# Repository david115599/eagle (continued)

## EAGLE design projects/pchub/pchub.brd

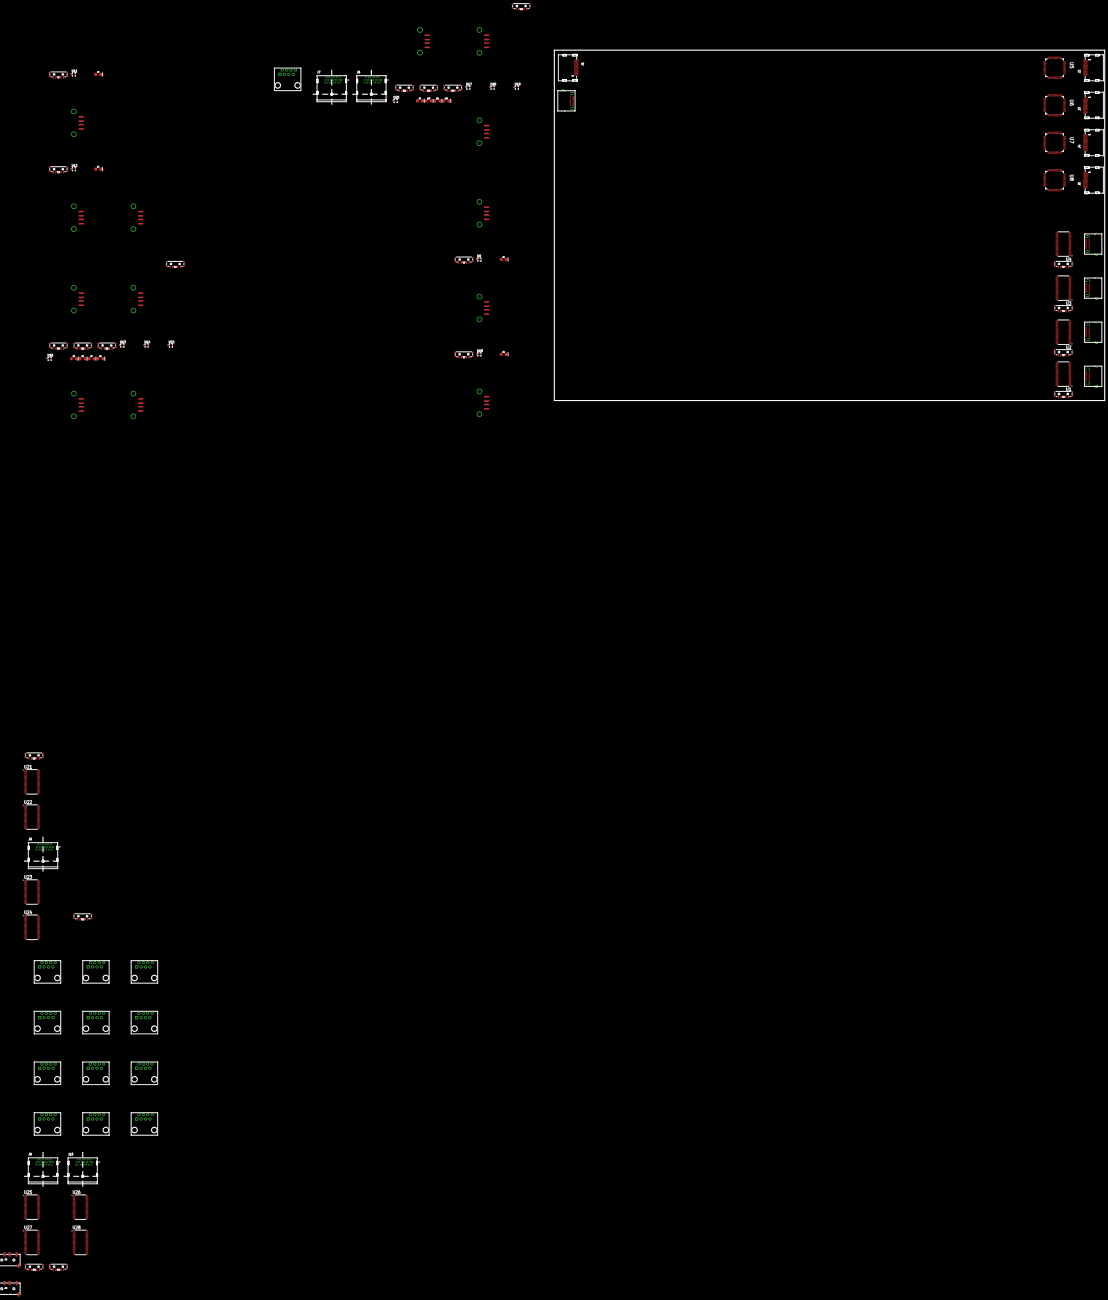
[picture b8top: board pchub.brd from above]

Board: 2 copper layers, 622.8 x 655.0 mm, 103 parts (0 on the bottom side), 383 nets, no tracks yet.

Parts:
D1, D2, D3, D4, D5, D6, D7, D8, D9, D10, D11, D12: FKIT-LED-1206
J1, J2, J3, J4, J5: 685119134923
J6, J7, J8, J9, J10: 2040210-1; TE_2040210-1
J11, J12: AUDIO_JACK_TRRSSMD_RA; AUDIO_JACK_3.5MM_TRRS_SMD_RA
S1, S2, S3, S4, S5, S6, S7, S8, S9, S10, S11, S12, S13, S14, S15, S16, S17, S18, S19, S20: SWITCH_SP3T_SMD
U1, U2, U3, U4, U21, U22, U23, U24, U25, U26, U27, U28: SN74CBT16214DGGR; SOP50P810X120-56N
U5, U6, U7, U8: TMDS361BPAG; QFP50P1200X1200X120-64N
U9, U10, U11, U12, U13, U14, U15, U16, U17, U18, U19, U20: FSUSB63UMX; QFN40P180X180X55-12N
U$1, U$2, U$3, U$4, U$5: USB-TYPE-C; USB-TYPE-C-SMT
U$6, U$19, U$20, U$21, U$22, U$23, U$24, U$25, U$26, U$27, U$28, U$29, U$30: RJ45-8PTH; RJ45-8
X1, X2, X3, X4, X5, X6, X7, X8, X9, X10, X11, X12, X13: USB; USB-A-S-NOSILK-FEMALE

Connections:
5.5V: S1.3, S2.3, S3.3, S4.3, U1.17, U2.17, U3.17, U4.17
B$1: U21.23, U23.23, U25.23, U27.23
B$2: U21.25, U23.25, U25.25, U27.25
CEC: J1.13, J2.13, J3.13, J4.13, J5.13
ETH1: U$6.1, U$19.1, U$20.1, U$21.1, U$22.1, U$23.1, U$24.1, U$25.1, U$26.1, U$27.1, U$28.1, U$29.1, U$30.1
ETH2: U$6.2, U$19.2, U$20.2, U$21.2, U$22.2, U$23.2, U$24.2, U$25.2, U$26.2, U$27.2, U$28.2, U$29.2, U$30.2
ETH3: U$6.3, U$19.3, U$20.3, U$21.3, U$22.3, U$23.3, U$24.3, U$25.3, U$26.3, U$27.3, U$28.3, U$29.3, U$30.3
ETH4: U$6.4, U$19.4, U$20.4, U$21.4, U$22.4, U$23.4, U$24.4, U$25.4, U$26.4, U$27.4, U$28.4, U$29.4, U$30.4
ETH5: U$6.5, U$19.5, U$20.5, U$21.5, U$22.5, U$23.5, U$24.5, U$25.5, U$26.5, U$27.5, U$28.5, U$29.5, U$30.5
ETH6: U$6.6, U$19.6, U$20.6, U$21.6, U$22.6, U$23.6, U$24.6, U$25.6, U$26.6, U$27.6, U$28.6, U$29.6, U$30.6
ETH7: U$6.7, U$19.7, U$20.7, U$21.7, U$22.7, U$23.7, U$24.7, U$25.7, U$26.7, U$27.7, U$28.7, U$29.7, U$30.7
ETH8: U$6.8, U$19.8, U$20.8, U$21.8, U$22.8, U$23.8, U$24.8, U$25.8, U$26.8, U$27.8, U$28.8, U$29.8, U$30.8
GND: U1.8, U1.19, U1.38, U1.49, U2.8, U2.19, U2.38, U2.49, U3.8, U3.19, U3.38, U3.49, U4.8, U4.19, U4.38, U4.49, U21.19, U22.19, U23.19, U24.19, U25.19, U26.19, U27.19, U28.19
GND-1: U21.38, U22.38, U23.38, U24.38, U25.38, U26.38, U27.38, U28.38
GND-2: U21.49, U22.49, U23.49, U24.49, U25.49, U26.49, U27.49, U28.49
GND-3: U21.8, U22.8, U23.8, U24.8, U25.8, U26.8, U27.8, U28.8
HDMIGND: J1.2, J1.5, J1.8, J1.11, J1.17, J1.SHELL, J1.SHELL1, J1.SHELL2, J1.SHELL3, J2.2, J2.5, J2.8, J2.11, J2.17, J2.SHELL, J2.SHELL1, J2.SHELL2, J2.SHELL3, J3.2, J3.5, J3.8, J3.11, J3.17, J3.SHELL, J3.SHELL1, J3.SHELL2, J3.SHELL3, J4.2, J4.5, J4.8, J4.11, J4.17, J4.SHELL, J4.SHELL1, J4.SHELL2, J4.SHELL3, J5.2, J5.5, J5.8, J5.11, J5.17, J5.SHELL, J5.SHELL1, J5.SHELL2, J5.SHELL3, U5.3, U5.9, U5.15, U5.22, U5.28, U5.43, U5.58, U6.3, U6.9, U6.15, U6.22, U6.28, U6.43, U6.58, U7.3, U7.9, U7.15, U7.22, U7.28, U7.43, U7.58, U8.3, U8.9, U8.15, U8.22, U8.28, U8.43, U8.58
HDMIVCC: J1.18, J2.18, J3.18, J4.18, J5.18, U5.6, U5.12, U5.19, U5.25, U5.40, U5.46, U5.55, U5.61, U6.6, U6.12, U6.19, U6.25, U6.40, U6.46, U6.55, U6.61, U7.6, U7.12, U7.19, U7.25, U7.40, U7.46, U7.55, U7.61, U8.6, U8.12, U8.19, U8.25, U8.40, U8.46, U8.55, U8.61
HEAC+: J1.14, J2.14, J3.14, J4.14, J5.14
unnamed: U2.18, U$2.5
unnamed: U2.23, U$2.3, U$2.B3
unnamed: U2.25, U$2.2, U$2.B2
unnamed: U2.27, U$2.1, U$2.12, U$2.B1, U$2.B12
unnamed: U2.2, U$2.P$1, U$2.P$2, U$2.P$3, U$2.P$4, U$2.P$5, U$2.P$6, U$2.P$7, U$2.P$8, U$2.P$9, U$2.P$10, U$2.P$11, U$2.P$12, U$2.P$13, U$2.P$14, U$2.P$15, U$2.P$16, U$2.P$17, U$2.P$18, U$2.P$19, U$2.P$20, U$2.P$21, U$2.P$22, U$2.P$23, U$2.P$24, U$2.P$25, U$2.P$26, U$2.P$27, U$2.P$28
unnamed: U2.4, U$2.B5
unnamed: U2.15, U$2.6, U$2.B6
unnamed: U2.13, U$2.7, U$2.B7
unnamed: U2.11, U$2.8, U$2.B8
unnamed: U2.9, U$2.10, U$2.B10
unnamed: U2.6, U$2.11, U$2.B11
unnamed: U3.18, U$4.5
unnamed: U3.23, U$4.3, U$4.B3
unnamed: U3.25, U$4.2, U$4.B2
unnamed: U3.27, U$4.1, U$4.12, U$4.B1, U$4.B12
unnamed: U3.2, U$4.P$1, U$4.P$2, U$4.P$3, U$4.P$4, U$4.P$5, U$4.P$6, U$4.P$7, U$4.P$8, U$4.P$9, U$4.P$10, U$4.P$11, U$4.P$12, U$4.P$13, U$4.P$14, U$4.P$15, U$4.P$16, U$4.P$17, U$4.P$18, U$4.P$19, U$4.P$20, U$4.P$21, U$4.P$22, U$4.P$23, U$4.P$24, U$4.P$25, U$4.P$26, U$4.P$27, U$4.P$28
unnamed: U3.4, U$4.B5
unnamed: U3.15, U$4.6, U$4.B6
unnamed: U3.13, U$4.7, U$4.B7
unnamed: U3.11, U$4.8, U$4.B8
unnamed: U3.9, U$4.10, U$4.B10
unnamed: U3.6, U$4.11, U$4.B11
unnamed: U4.18, U$5.5
unnamed: U4.23, U$5.3, U$5.B3
unnamed: U4.25, U$5.2, U$5.B2
unnamed: U4.27, U$5.1, U$5.12, U$5.B1, U$5.B12
unnamed: U4.2, U$5.P$1, U$5.P$2, U$5.P$3, U$5.P$4, U$5.P$5, U$5.P$6, U$5.P$7, U$5.P$8, U$5.P$9, U$5.P$10, U$5.P$11, U$5.P$12, U$5.P$13, U$5.P$14, U$5.P$15, U$5.P$16, U$5.P$17, U$5.P$18, U$5.P$19, U$5.P$20, U$5.P$21, U$5.P$22, U$5.P$23, U$5.P$24, U$5.P$25, U$5.P$26, U$5.P$27, U$5.P$28
unnamed: U4.4, U$5.B5
unnamed: U4.15, U$5.6, U$5.B6
unnamed: U4.13, U$5.7, U$5.B7
unnamed: U4.11, U$5.8, U$5.B8
unnamed: U4.9, U$5.10, U$5.B10
unnamed: U4.6, U$5.11, U$5.B11
unnamed: S2.4, U2.56
unnamed: S1.4, U1.56
unnamed: S1.2, U1.55
unnamed: S1.1, U1.1
unnamed: S2.2, U2.55
unnamed: S2.1, U2.1
unnamed: S3.4, U4.56
unnamed: S3.2, U4.55
unnamed: S3.1, U4.1
unnamed: S4.4, U3.56
unnamed: S4.2, U3.55
unnamed: S4.1, U3.1
unnamed: J2.3, U5.18
unnamed: J2.1, U5.17
unnamed: J2.6, U5.21
unnamed: J2.4, U5.20
unnamed: J2.9, U5.24
unnamed: J2.7, U5.23
unnamed: J2.12, U5.27
unnamed: J2.10, U5.26
unnamed: J2.19, U5.31
unnamed: J3.3, U6.18
unnamed: J3.1, U6.17
unnamed: J3.6, U6.21
unnamed: J3.4, U6.20
unnamed: J3.9, U6.24
unnamed: J3.7, U6.23
unnamed: J3.12, U6.27
unnamed: J3.10, U6.26
unnamed: J3.19, U6.31
unnamed: J4.3, U7.18
unnamed: J4.1, U7.17
unnamed: J4.6, U7.21
unnamed: J4.4, U7.20
unnamed: J4.9, U7.24
unnamed: J4.7, U7.23
unnamed: J4.12, U7.27
unnamed: J4.10, U7.26
unnamed: J4.19, U7.31
unnamed: J5.3, U8.18
unnamed: J5.1, U8.17
unnamed: J5.6, U8.21
unnamed: J5.4, U8.20
unnamed: J5.9, U8.24
unnamed: J5.7, U8.23
unnamed: J5.12, U8.27
unnamed: J5.10, U8.26
unnamed: J5.19, U8.31
unnamed: U9.2, X1.D-
unnamed: U9.1, X1.D+
unnamed: D1.C, S5.1, U9.4
unnamed: U10.2, X3.D-
unnamed: U10.1, X3.D+
unnamed: D1.A, S5.2, S5.4, U9.11
unnamed: D2.C, S6.1, U10.4
unnamed: D2.A, S6.2, S6.4, U10.11
unnamed: U11.2, X4.D-
unnamed: U11.1, X4.D+
unnamed: D3.C, S7.1, U11.4
unnamed: D3.A, S7.2, S7.4, U11.11
unnamed: U12.2, X5.D-
unnamed: U12.1, X5.D+
unnamed: D4.C, S8.1, U12.4
unnamed: D4.A, S8.2, S8.4, U12.11
unnamed: U13.2, X6.D-
unnamed: U13.1, X6.D+
unnamed: D5.C, S9.1, U13.4
unnamed: D5.A, S9.2, S9.4, U13.11
unnamed: U14.2, X7.D-
unnamed: U14.1, X7.D+
unnamed: D6.C, S10.1, U14.4
unnamed: D6.A, S10.2, S10.4, U14.11
unnamed: U15.2, X8.D-
unnamed: U15.1, X8.D+
unnamed: D7.C, S11.1, U15.4
unnamed: D7.A, S11.2, S11.4, U15.11
unnamed: U16.2, X9.D-
unnamed: U16.1, X9.D+
unnamed: D8.C, S12.1, U16.4
unnamed: D8.A, S12.2, S12.4, U16.11
unnamed: U17.2, X10.D-
unnamed: U17.1, X10.D+
unnamed: D9.C, S13.1, U17.4
unnamed: D9.A, S13.2, S13.4, U17.11
unnamed: U18.2, X11.D-
unnamed: U18.1, X11.D+
unnamed: D10.C, S14.1, U18.4
unnamed: D10.A, S14.2, S14.4, U18.11
unnamed: U19.2, X12.D-
unnamed: U19.1, X12.D+
unnamed: D11.C, S15.1, U19.4
unnamed: D11.A, S15.2, S15.4, U19.11
unnamed: U20.2, X13.D-
unnamed: U20.1, X13.D+
unnamed: D12.C, S16.1, U20.4
unnamed: D12.A, S16.2, S16.4, U20.11
unnamed: J7.1, U21.2
unnamed: J7.2, U21.4
unnamed: U1.18, U$3.5
unnamed: U1.23, U$3.3, U$3.B3
unnamed: U1.25, U$3.2, U$3.B2
unnamed: U1.27, U$3.1, U$3.12, U$3.B1, U$3.B12
unnamed: U1.2, U$3.P$1, U$3.P$2, U$3.P$3, U$3.P$4, U$3.P$5, U$3.P$6, U$3.P$7, U$3.P$8, U$3.P$9, U$3.P$10, U$3.P$11, U$3.P$12, U$3.P$13, U$3.P$14, U$3.P$15, U$3.P$16, U$3.P$17, U$3.P$18, U$3.P$19, U$3.P$20, U$3.P$21, U$3.P$22, U$3.P$23, U$3.P$24, U$3.P$25, U$3.P$26, U$3.P$27, U$3.P$28
unnamed: U1.4, U$3.B5
unnamed: U1.15, U$3.6, U$3.B6
unnamed: U1.13, U$3.7, U$3.B7
unnamed: U1.11, U$3.8, U$3.B8
unnamed: U1.9, U$3.10, U$3.B10
unnamed: U1.6, U$3.11, U$3.B11
unnamed: J7.3, U21.6
unnamed: J7.4, U21.9
unnamed: J7.5, U21.11
unnamed: J7.6, U21.13
unnamed: J7.7, U21.15
unnamed: J7.8, U21.18
unnamed: J7.9, U21.21
unnamed: J7.12, U21.27
unnamed: J7.13, U22.2
unnamed: J7.14, U22.4
unnamed: J7.15, U22.6
unnamed: J7.16, U22.9
unnamed: J7.17, U22.11
unnamed: J7.18, U22.13
unnamed: J7.19, U22.15
unnamed: J7.SH1, J7.SH2, J7.SH3, J7.SH4, U22.21
unnamed: J8.1, U23.2
unnamed: J8.2, U23.4
unnamed: J7.20, U22.18
unnamed: J8.3, U23.6
unnamed: J8.4, U23.9
unnamed: J8.5, U23.11
unnamed: J8.6, U23.13
unnamed: J8.7, U23.15
unnamed: J8.8, U23.18
unnamed: J8.9, U23.21
unnamed: J8.12, U23.27
unnamed: J8.13, U24.2
unnamed: J8.14, U24.4
unnamed: J8.15, U24.6
unnamed: J8.16, U24.9
unnamed: J8.17, U24.11
unnamed: J8.18, U24.13
unnamed: J8.19, U24.15
unnamed: J8.SH1, J8.SH2, J8.SH3, J8.SH4, U24.21
unnamed: J8.20, U24.18
unnamed: J9.1, U25.2
unnamed: J9.2, U25.4
unnamed: J9.3, U25.6
unnamed: J9.4, U25.9
unnamed: J9.5, U25.11
unnamed: J9.6, U25.13
unnamed: J9.7, U25.15
unnamed: J9.8, U25.18
unnamed: J9.9, U25.21
unnamed: J9.12, U25.27
unnamed: J9.13, U26.2
unnamed: J9.14, U26.4
unnamed: J9.15, U26.6
unnamed: J9.16, U26.9
unnamed: J9.17, U26.11
unnamed: J9.18, U26.13
unnamed: J9.19, U26.15
unnamed: J9.SH1, J9.SH2, J9.SH3, J9.SH4, U26.21
unnamed: J9.20, U26.18
unnamed: J10.1, U27.2
unnamed: J10.2, U27.4
unnamed: J10.3, U27.6
unnamed: J10.4, U27.9
unnamed: J10.5, U27.11
unnamed: J10.6, U27.13
unnamed: J10.7, U27.15
unnamed: J10.8, U27.18
unnamed: J10.9, U27.21
unnamed: J10.12, U27.27
unnamed: J10.13, U28.2
unnamed: J10.14, U28.4
unnamed: J10.15, U28.6
unnamed: J10.16, U28.9
unnamed: J10.17, U28.11
unnamed: J10.18, U28.13
unnamed: J10.19, U28.15
unnamed: J10.SH1, J10.SH2, J10.SH3, J10.SH4, U28.21
unnamed: J10.20, U28.18
PC1A1: J11.RING2, J12.RING2
PC1A2: J11.TIP, J12.TIP
PC1A3: J11.RING1, J12.RING1
PC1A4: J11.EARTH, J12.EARTH
PC1D+: U9.6, U10.6, U11.6, U12.6, U13.6, U14.6, U15.6, U16.6, U17.6, U18.6, U19.6, U20.6, X2.D+
PC1D-: U9.5, U10.5, U11.5, U12.5, U13.5, U14.5, U15.5, U16.5, U17.5, U18.5, U19.5, U20.5, X2.D-
PC1DP1: J6.1, U21.54, U23.54, U25.54, U27.54
PC1DP2: J6.2, U21.52, U23.52, U25.52, U27.52
PC1DP3: J6.3, U21.50, U23.50, U25.50, U27.50
PC1DP4: J6.4, U21.47, U23.47, U25.47, U27.47
PC1DP5: J6.5, U21.45, U23.45, U25.45, U27.45
PC1DP6: J6.6, U21.43, U23.43, U25.43, U27.43
PC1DP7: J6.7, U21.41, U23.41, U25.41, U27.41
PC1DP8: J6.8, U21.39, U23.39, U25.39, U27.39
PC1DP9: J6.9, U21.36, U23.36, U25.36, U27.36
PC1DP10: J6.10, U21.34, U23.34, U25.34, U27.34
PC1DP11: J6.11, U21.32, U23.32, U25.32, U27.32
PC1DP12: J6.12, U21.30, U23.30, U25.30, U27.30
PC1DP13: J6.13, U22.54, U24.54, U26.54, U28.54
PC1DP14: J6.14, U22.52, U24.52, U26.52, U28.52
PC1DP15: J6.15, U22.50, U24.50, U26.50, U28.50
PC1DP16: J6.16, U22.47, U24.47, U26.47, U28.47
PC1DP17: J6.17, U22.45, U24.45, U26.45, U28.45
PC1DP18: J6.18, U22.43, U24.43, U26.43, U28.43
PC1DP19: J6.19, U22.41, U24.41, U26.41, U28.41
PC1DP20: J6.20, U22.39, U24.39, U26.39, U28.39
PC1DPS: J6.SH1, J6.SH2, J6.SH3, J6.SH4, U22.36, U24.36, U26.36, U28.36
PC1HDMI-HOT: J1.19, U5.35, U6.35, U7.35, U8.35
PC1HDMI-SCL: J1.15, U5.37, U6.37, U7.37, U8.37
PC1HDMI-SDA: J1.16, U5.36, U6.36, U7.36, U8.36
PC1HDMI-TMDS1+: J1.4, U5.45, U6.45, U7.45, U8.45
PC1HDMI-TMDS1-: J1.6, U5.44, U6.44, U7.44, U8.44
PC1HDMI-TMDSC+: J1.10, U5.39, U6.39, U7.39, U8.39
PC1HDMI-TMDSC-: J1.12, U5.38, U6.38, U7.38, U8.38
PC1HDMI-TMDSD0+: J1.7, U5.42, U6.42, U7.42, U8.42
PC1HDMI-TMDSD0-: J1.9, U5.41, U6.41, U7.41, U8.41
PC1HDMI-TMDSD2+: J1.1, U5.48, U6.48, U7.48, U8.48
PC1HDMI-TMDSD2-: J1.3, U5.47, U6.47, U7.47, U8.47
PC1USBC-CC1: U1.39, U2.39, U3.39, U4.39, U$1.5
PC1USBC-CC2: U1.52, U2.52, U3.52, U4.52, U$1.B5
PC1USBC-D+: U1.41, U2.41, U3.41, U4.41, U$1.6, U$1.B6
PC1USBC-D-: U1.43, U2.43, U3.43, U4.43, U$1.7, U$1.B7
PC1USBC-GND: U1.30, U2.30, U3.30, U4.30, U$1.1, U$1.12, U$1.B1, U$1.B12
PC1USBC-SBU: U1.45, U2.45, U3.45, U4.45, U$1.8, U$1.B8
PC1USBC-SHIELD: U1.54, U2.54, U3.54, U4.54, U$1.P$1, U$1.P$2, U$1.P$3, U$1.P$4, U$1.P$5, U$1.P$6, U$1.P$7, U$1.P$8, U$1.P$9, U$1.P$10, U$1.P$11, U$1.P$12, U$1.P$13, U$1.P$14, U$1.P$15, U$1.P$16, U$1.P$17, U$1.P$18, U$1.P$19, U$1.P$20, U$1.P$21, U$1.P$22, U$1.P$23, U$1.P$24, U$1.P$25, U$1.P$26, U$1.P$27, U$1.P$28
PC1USBC-SSRX+: U1.50, U2.50, U3.50, U4.50, U$1.11, U$1.B11
PC1USBC-SSRX-: U1.47, U2.47, U3.47, U4.47, U$1.10, U$1.B10
PC1USBC-SSTX+: U1.32, U2.32, U3.32, U4.32, U$1.2, U$1.B2
PC1USBC-SSTX-: U1.34, U2.34, U3.34, U4.34, U$1.3, U$1.B3
PC1USBC-VBUS: U1.36, U2.36, U3.36, U4.36, U$1.4, U$1.9, U$1.B4, U$1.B9
PC2D+: U9.8, U10.8, U11.8, U12.8, U13.8, U14.8, U15.8, U16.8, U17.8, U18.8, U19.8, U20.8
PC2D-: U9.7, U10.7, U11.7, U12.7, U13.7, U14.7, U15.7, U16.7, U17.7, U18.7, U19.7, U20.7
PC2DP1: U21.53, U23.53, U25.53, U27.53
PC2DP2: U21.51, U23.51, U25.51, U27.51
PC2DP3: U21.48, U23.48, U25.48, U27.48
PC2DP4: U21.46, U23.46, U25.46, U27.46
PC2DP5: U21.44, U23.44, U25.44, U27.44
PC2DP6: U21.42, U23.42, U25.42, U27.42
PC2DP7: U21.40, U23.40, U25.40, U27.40
PC2DP8: U21.37, U23.37, U25.37, U27.37
PC2DP9: U21.35, U23.35, U25.35, U27.35
PC2DP10: U21.33, U23.33, U25.33, U27.33
PC2DP11: U21.31, U23.31, U25.31, U27.31
PC2DP12: U21.29, U23.29, U25.29, U27.29
PC2DP13: U22.53, U24.53, U26.53, U28.53
PC2DP14: U22.51, U24.51, U26.51, U28.51
PC2DP15: U22.48, U24.48, U26.48, U28.48
PC2DP16: U22.46, U24.46, U26.46, U28.46
PC2DP17: U22.44, U24.44, U26.44, U28.44
PC2DP18: U22.42, U24.42, U26.42, U28.42
PC2DP19: U22.40, U24.40, U26.40, U28.40
PC2DP20: U22.37, U24.37, U26.37, U28.37
PC2DPS: U22.35, U24.35, U26.35, U28.35
PC2HDMI-HOT: U5.50, U6.50, U7.50, U8.50
PC2HDMI-SCL: U5.2, U6.2, U7.2, U8.2
PC2HDMI-SDA: U5.51, U6.51, U7.51, U8.51
PC2HDMI-TMDS1+: U5.60, U6.60, U7.60, U8.60
PC2HDMI-TMDS1-: U5.59, U6.59, U7.59, U8.59
PC2HDMI-TMDSC+: U5.54, U6.54, U7.54, U8.54
PC2HDMI-TMDSC-: U5.53, U6.53, U7.53, U8.53
PC2HDMI-TMDSD0+: U5.57, U6.57, U7.57, U8.57
PC2HDMI-TMDSD0-: U5.56, U6.56, U7.56, U8.56
PC2HDMI-TMDSD2+: U5.63, U6.63, U7.63, U8.63
PC2HDMI-TMDSD2-: U5.62, U6.62, U7.62, U8.62
PC2USBC-CC1: U1.37, U2.37, U3.37, U4.37
PC2USBC-CC2: U1.51, U2.51, U3.51, U4.51
PC2USBC-D+: U1.40, U2.40, U3.40, U4.40
PC2USBC-D-: U1.42, U2.42, U3.42, U4.42
PC2USBC-GND: U1.29, U2.29, U3.29, U4.29
PC2USBC-SBU: U1.44, U2.44, U3.44, U4.44
PC2USBC-SHIELD: U1.53, U2.53, U3.53, U4.53
PC2USBC-SSRX+: U1.48, U2.48, U3.48, U4.48
PC2USBC-SSRX-: U1.46, U2.46, U3.46, U4.46
PC2USBC-SSTX+: U1.31, U2.31, U3.31, U4.31
PC2USBC-SSTX-: U1.33, U2.33, U3.33, U4.33
PC2USBC-VBUS: U1.35, U2.35, U3.35, U4.35
PC3D+: U9.10, U10.10, U11.10, U12.10, U13.10, U14.10, U15.10, U16.10, U17.10, U18.10, U19.10, U20.10
PC3D-: U9.9, U10.9, U11.9, U12.9, U13.9, U14.9, U15.9, U16.9, U17.9, U18.9, U19.9, U20.9
PC3DP1: U21.3, U23.3, U25.3, U27.3
PC3DP2: U21.5, U23.5, U25.5, U27.5
PC3DP3: U21.7, U23.7, U25.7, U27.7
PC3DP4: U21.10, U23.10, U25.10, U27.10
PC3DP5: U21.12, U23.12, U25.12, U27.12
PC3DP6: U21.14, U23.14, U25.14, U27.14
PC3DP7: U21.16, U23.16, U25.16, U27.16
PC3DP8: U21.20, U23.20, U25.20, U27.20
PC3DP9: U21.22, U23.22, U25.22, U27.22
PC3DP10: U21.24, U23.24, U25.24, U27.24
PC3DP11: U21.26, U23.26, U25.26, U27.26
PC3DP12: U21.28, U23.28, U25.28, U27.28
PC3DP13: U22.3, U24.3, U26.3, U28.3
PC3DP14: U22.5, U24.5, U26.5, U28.5
PC3DP15: U22.7, U24.7, U26.7, U28.7
PC3DP16: U22.10, U24.10, U26.10, U28.10
PC3DP17: U22.12, U24.12, U26.12, U28.12
PC3DP18: U22.14, U24.14, U26.14, U28.14
PC3DP19: U22.16, U24.16, U26.16, U28.16
PC3DP20: U22.20, U24.20, U26.20, U28.20
PC3DPS: U22.22, U24.22, U26.22, U28.22
PC3HDMI-HOT: U5.64, U6.64, U7.64, U8.64
PC3HDMI-SCL: U5.52, U6.52, U7.52, U8.52
PC3HDMI-SDA: U5.1, U6.1, U7.1, U8.1
PC3HDMI-TMDS1+: U5.11, U6.11, U7.11, U8.11
PC3HDMI-TMDS1-: U5.10, U6.10, U7.10, U8.10
PC3HDMI-TMDSC+: U5.5, U6.5, U7.5, U8.5
PC3HDMI-TMDSC-: U5.4, U6.4, U7.4, U8.4
PC3HDMI-TMDSD0+: U5.8, U6.8, U7.8, U8.8
PC3HDMI-TMDSD0-: U5.7, U6.7, U7.7, U8.7
PC3HDMI-TMDSD2+: U5.14, U6.14, U7.14, U8.14
PC3HDMI-TMDSD2-: U5.13, U6.13, U7.13, U8.13
PC3USBC-CC1: U1.20, U2.20, U3.20, U4.20
PC3USBC-CC2: U1.5, U2.5, U3.5, U4.5
PC3USBC-D+: U1.16, U2.16, U3.16, U4.16
PC3USBC-D-: U1.14, U2.14, U3.14, U4.14
PC3USBC-GND: U1.28, U2.28, U3.28, U4.28
PC3USBC-SBU: U1.12, U2.12, U3.12, U4.12
PC3USBC-SHIELD: U1.3, U2.3, U3.3, U4.3
PC3USBC-SSRX+: U1.7, U2.7, U3.7, U4.7
PC3USBC-SSRX-: U1.10, U2.10, U3.10, U4.10
PC3USBC-SSTX+: U1.26, U2.26, U3.26, U4.26
PC3USBC-SSTX-: U1.24, U2.24, U3.24, U4.24
PC3USBC-VBUS: U1.22, U2.22, U3.22, U4.22
SCL: J2.15, J3.15, J4.15, J5.15, U5.29, U6.29, U7.29, U8.29
SDA: J2.16, J3.16, J4.16, J5.16, U5.30, U6.30, U7.30, U8.30
USBGND: U9.3, U10.3, U11.3, U12.3, U13.3, U14.3, U15.3, U16.3, U17.3, U18.3, U19.3, U20.3, X1.GND, X2.GND, X3.GND, X4.GND, X5.GND, X6.GND, X7.GND, X8.GND, X9.GND, X10.GND, X11.GND, X12.GND, X13.GND
USBVCC: S5.3, S6.3, S7.3, S8.3, S9.3, S10.3, S11.3, S12.3, S13.3, S14.3, S15.3, S16.3, U9.12, U10.12, U11.12, U12.12, U13.12, U14.12, U15.12, U16.12, U17.12, U18.12, U19.12, U20.12, X1.VBUS, X2.VBUS, X3.VBUS, X4.VBUS, X5.VBUS, X6.VBUS, X7.VBUS, X8.VBUS, X9.VBUS, X10.VBUS, X11.VBUS, X12.VBUS, X13.VBUS
VBUS: U1.21, U2.21, U3.21, U4.21, U$2.4, U$2.9, U$2.B4, U$2.B9, U$3.4, U$3.9, U$3.B4, U$3.B9, U$4.4, U$4.9, U$4.B4, U$4.B9, U$5.4, U$5.9, U$5.B4, U$5.B9
VCC: U21.17, U22.17, U23.17, U24.17, U25.17, U26.17, U27.17, U28.17
